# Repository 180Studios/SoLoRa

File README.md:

Board Features:

1. Low-cost components 

2. Easy (ish) Assembly. 
    a. Uses QFP package processor and 0603 Rs and Cs 
    b. Can be soldered by hand by most people using standard soldering iron 
    c. One exception is the accelerometer, which can be soldered using a reflow heat gun and a little training

3. Arduino compatible 
    a. Uses the same device as the Arduino Zero - can use Arduino bootloader. 

4. FeatherWing compatible 
    a. Can use with Adafruit’s featherwing expansion boards or use the header for a protoboard mezzanine 

5. Multiple power options to targeting wider IoT applications, particular field applications 
    a. Solar 
        i. Has a CR123 battery clip for a LiFePo4 battery used as a power reservoir. (400mAh) 
        ii. On-board regulator charges LiFePo4 to constant voltage. Solar cell size constrains max charge current. 
    b. Rechargeable Li-Po or external battery pack 
        i. For standard indoor applications 
        ii. On-board USB micro connector and charger IC 
    c. Lithium (primary cell) 
        i. Battery clip will also house a standard CR123 3V Lithium, which has ~1000mAH capacity 
    d. USB 5V for desktop development (or use with a USB battery bank?) 
    e. On- board adjustable regulator 
        i. Change Resistor values to adjust VDD 
            1. To drop Li-Po, external battery pack output voltage and USB 5V to safe level 
            2. LiFePo4 charge voltage. 
        ii. Regulator is used with Lithium primary battery 

6. Small size: 2.3 x 2 inches 
    a. Has mounting holes to match a inexpensive water tight enclosure 
    b. All components mount on one-size only. Bottom is free to increase mounting versatility. 
    c. 2-layer board, cheaper to fabricate. 

7. ARM Cortex M0 (SAMD20G18A) 

    a. Low power, high speed capable, 256K Flash 

8. Optional on-board sensors, indicators 
    a. 3-Axis Accelerometer 
    b. Temperature 
    c. Programmable Red LED 

9. Development Options 
    a. Arduino IDE (use as an Arduino Zero) 
    b. Atmel Studio 
        i. Atmel Studio has Arduino templates to program like Arduino, or: 
        ii. Use standard C form 
        iii. Full debugging capability (breakpoints, watch variables) 
            1. $20 JTAG debugger hardware required for this feature

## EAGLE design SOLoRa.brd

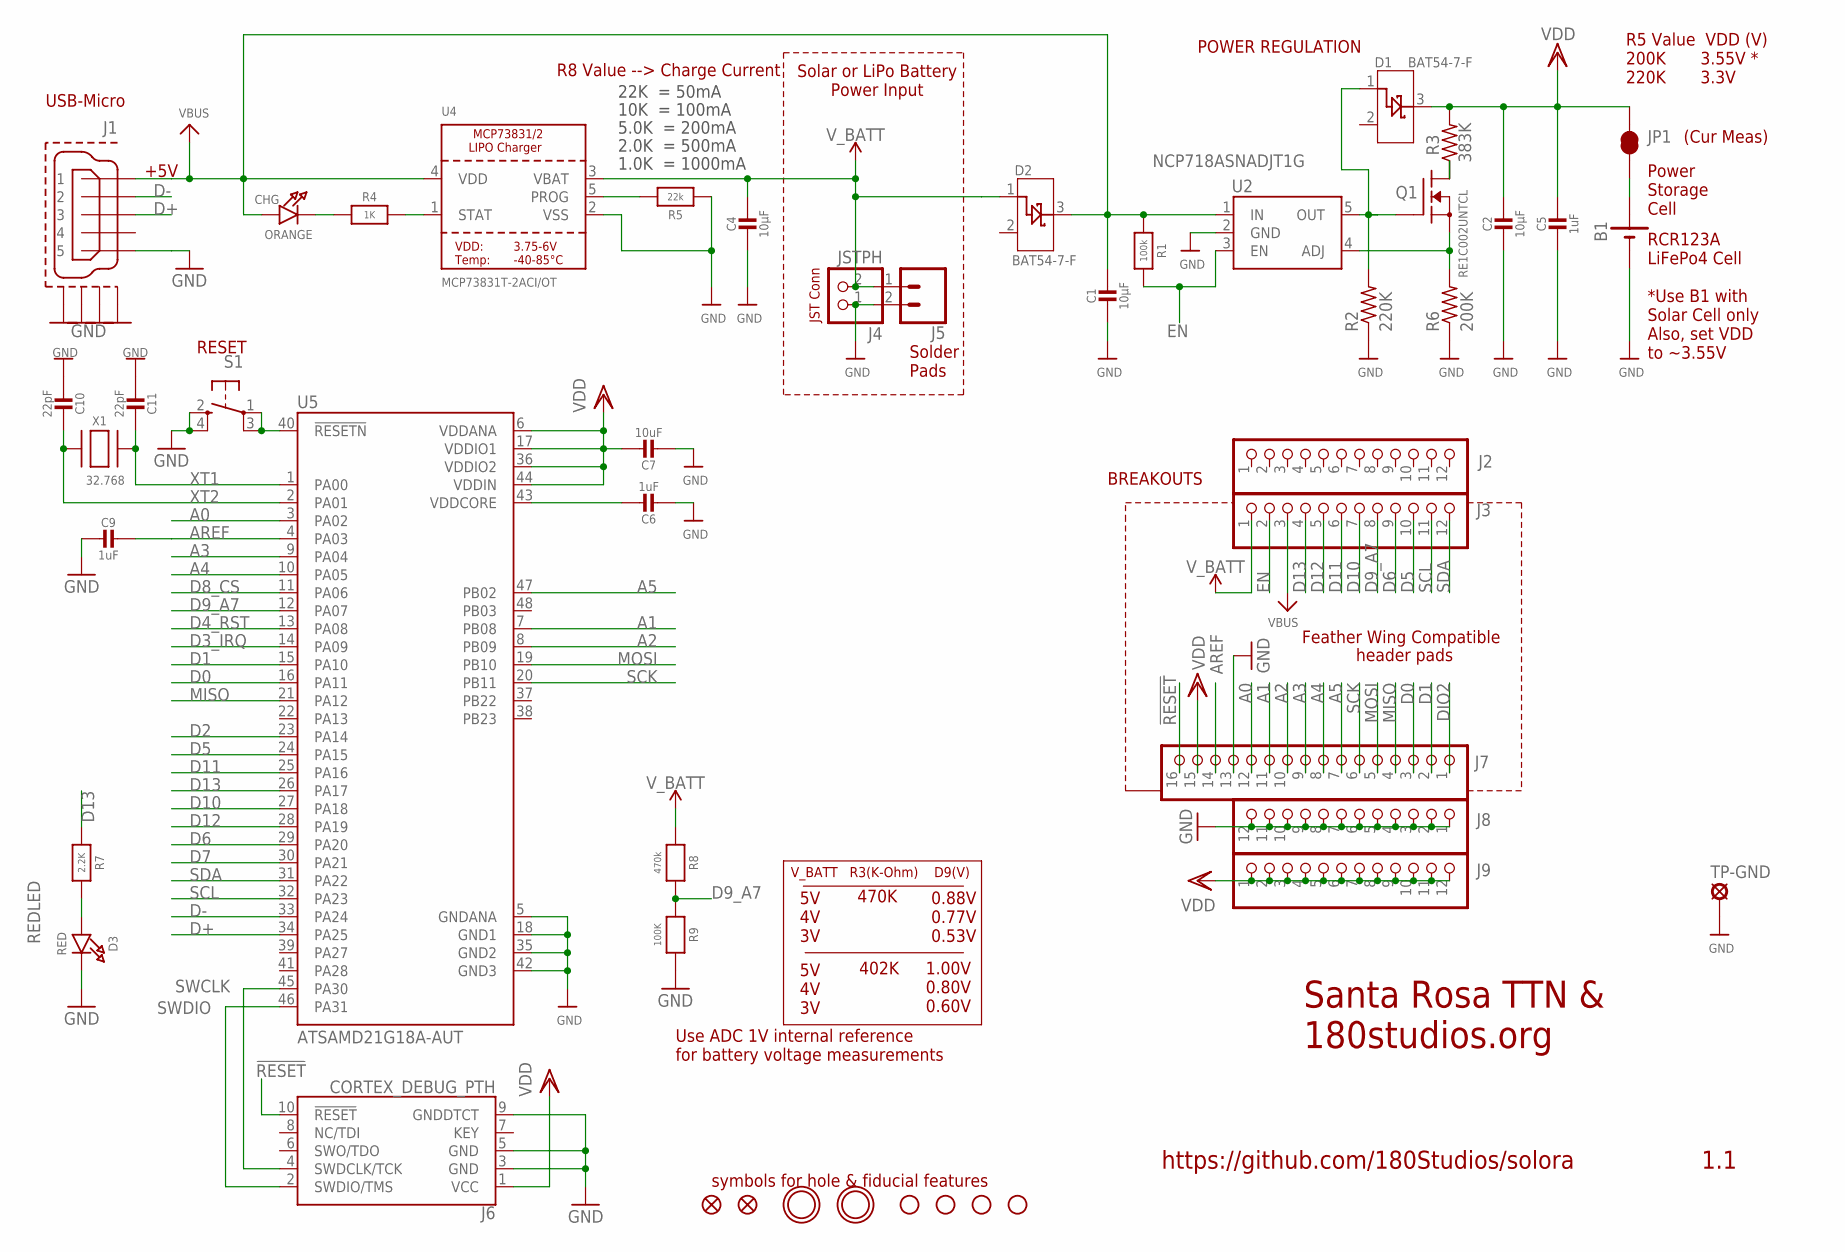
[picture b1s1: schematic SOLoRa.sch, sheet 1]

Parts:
$$U$1, $$U$4: FIDUCIAL""; FIDUCIAL_1MM
$$U$2, $$U$3: MOUNTINGHOLE2.5; MOUNTINGHOLE_2.5_PLATED
B1: BH123A
C1, C2, C4: 10µF; 0805-NO
C5, C6, C9: 1uF; 0603-NO
C7: 10uF; 0805-NO
C10, C11: 22pF; 0603-NO
CHG: ORANGE; CHIPLED_0805_NOOUTLINE
D1, D2: BAT54-7-F; SOT-23
D3: RED; CHIPLED_0805_NOOUTLINE
H1, H2, H3, H4: STAND-OFF
J1: CONN_USB-MIRCO_10118194; 10118194_USB
J2, J3, J8, J9: HEADER-1X12; 1X12_ROUND
J4: JSTPH; JSTPH2
J5: CONN_021X02_NO_SILK; 1X02_NO_SILK
J6: CORTEX_DEBUG_PTH; 2X5-PTH-1.27MM
J7: HEADER-1X16ROUND; 1X16_ROUND
JP1: JUMPER-SMT_2_NC_TRACE_NO-SILK; SMT-JUMPER_2_NC_TRACE_NO-SILK
Q1: RE1C002UNTCL; SOT50P160X85-3N
R1: 100k; 0603-NO
R2: 220K; R0603
R3: 383K; R0603
R4: 1K; 0603-NO
R5: 22k; 0603-NO
R6: 200K; R0603
R7: 2.2K; 0603-NO
R8: 470k; 0603-NO
R9: 100K; 0603-NO
S1: SPST_TACT-KMR2; KMR2
TP-GND: SE14
U2: NCP718ASNADJT1G; SOT95P280X100-5N
U4: MCP73831T-2ACI/OT; SOT23-5
U5: ATSAMD21G18A-AUT; QFP50P900X900X120-48N
X1: 32.768; XTAL3215

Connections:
!RESET: J6.10 (!RESET), J7.16, S1.1, S1.3 (P1), U5.40 (!RESETN)
A0: J7.12, U5.3 (PA02)
A1: J7.11, U5.7 (PB08)
A2: J7.10, U5.8 (PB09)
A3: J7.9, U5.9 (PA04)
A4: J7.8, U5.10 (PA05)
A5: J7.7, U5.47 (PB02)
ADJ1: Q1.3 (D), R3.1
AREF: C9.1, J7.14, U5.4 (PA03)
CHGLED: CHG.C, R4.1
D0: J7.3, U5.16 (PA11)
D1: J7.2, U5.15 (PA10)
D2: U5.23 (PA14)
D3_IRQ: U5.14 (PA09); also elsewhere on the board
D4_RST: U5.13 (PA08); also elsewhere on the board
D5: J3.10, U5.24 (PA15)
D6: J3.9, U5.29 (PA20); also elsewhere on the board
D7: U5.30 (PA21)
D8_CS: U5.11 (PA06); also elsewhere on the board
D9_A7: J3.8, R8.2, R9.1, U5.12 (PA07)
D10: J3.7, U5.27 (PA18)
D11: J3.6, U5.25 (PA16); also elsewhere on the board
D12: J3.5, U5.28 (PA19)
D13: J3.4, R7.1, U5.26 (PA17)
D+: J1.3, U5.34 (PA25)
D-: J1.2, U5.33 (PA24)
DIO2: J7.1; also elsewhere on the board
EN: J3.2, R1.2, U2.3 (EN)
GND: B1.MINUS, C1.2, C2.2, C4.2, C5.2, C6.2, C7.2, C9.2, C10.2, C11.2, D3.C, J1.5, J1.6 (GND1), J1.7 (GND2), J1.8 (GND3), J1.9 (GND4), J4.1, J5.2, J6.3 (GND), J6.5 (GND), J6.9 (GNDDTCT), J7.13, J8.1, J8.2, J8.3, J8.4, J8.5, J8.6, J8.7, J8.8, J8.9, J8.10, J8.11, J8.12, R2.1, R5.2, R6.1, R9.2, S1.2 (S), S1.4 (S1), TP-GND.MP, U2.2 (GND), U4.2 (VSS), U5.5 (GNDANA), U5.18 (GND1), U5.35 (GND2), U5.42 (GND3); also elsewhere on the board
MISO: J7.4, U5.21 (PA12); also elsewhere on the board
MOSI: J7.5, U5.19 (PB10); also elsewhere on the board
PLUS: B1.PLUS, JP1.1
PROG: R5.1, U4.5 (PROG)
REDLED: D3.A, R7.2
REGADJ: Q1.2 (S), R6.2, U2.4 (ADJ)
REGOUT: D1.1 (EPAD1), Q1.1 (G), R2.2, U2.5 (OUT)
SCK: J7.6, U5.20 (PB11); also elsewhere on the board
SCL: J3.11, U5.32 (PA23); also elsewhere on the board
SDA: J3.12, U5.31 (PA22); also elsewhere on the board
STAT: R4.2, U4.1 (STAT)
SWCLK: J6.4 (SWDCLK/TCK), U5.45 (PA30)
SWDIO: J6.2 (SWDIO/TMS), U5.46 (PA31)
VBUS: C1.1, CHG.A, D2.3 (EPAD3), J1.1, J3.3, R1.1, U2.1 (IN), U4.4 (VDD)
VDD: C2.1, C5.1, C7.1, D1.3 (EPAD3), J6.1 (VCC), J7.15, J9.1, J9.2, J9.3, J9.4, J9.5, J9.6, J9.7, J9.8, J9.9, J9.10, J9.11, J9.12, JP1.2, R3.2, U5.6 (VDDANA), U5.17 (VDDIO1), U5.36 (VDDIO2), U5.44 (VDDIN); also elsewhere on the board
VDDCORE: C6.1, U5.43 (VDDCORE)
V_BATT: C4.1, D2.1 (EPAD1), J3.1, J4.2, J5.1, R8.1, U4.3 (VBAT)
XT1: C11.1, U5.1 (PA00), X1.P$1
XT2: C10.1, U5.2 (PA01), X1.P$2

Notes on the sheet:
POWER REGULATION
RESET
10K = 100mA
5.0K = 200mA
2.0K = 500mA
1.0K = 1000mA
BREAKOUTS
R5 Value VDD (V) 200K 3.55V * 220K 3.3V
22K = 50mA
RCR123A LiFePo4 Cell *Use B1 with Solar Cell only Also, set VDD to ~3.55V
Solar or LiPo Battery Power Input
Power Storage Cell
JST Conn
Solder Pads
R8 Value --> Charge Current
1.1
Santa Rosa TTN & 180studios.org
https://github.com/180Studios/solora
USB-Micro
+5V
Feather Wing Compatible
header pads
V_BATT R3(K-Ohm) D9(V)
5V 4V 3V
470K
402K
0.88V 0.77V 0.53V
1.00V 0.80V 0.60V
Use ADC 1V internal reference for battery voltage measurements
symbols for hole & fiducial features
(Cur Meas)

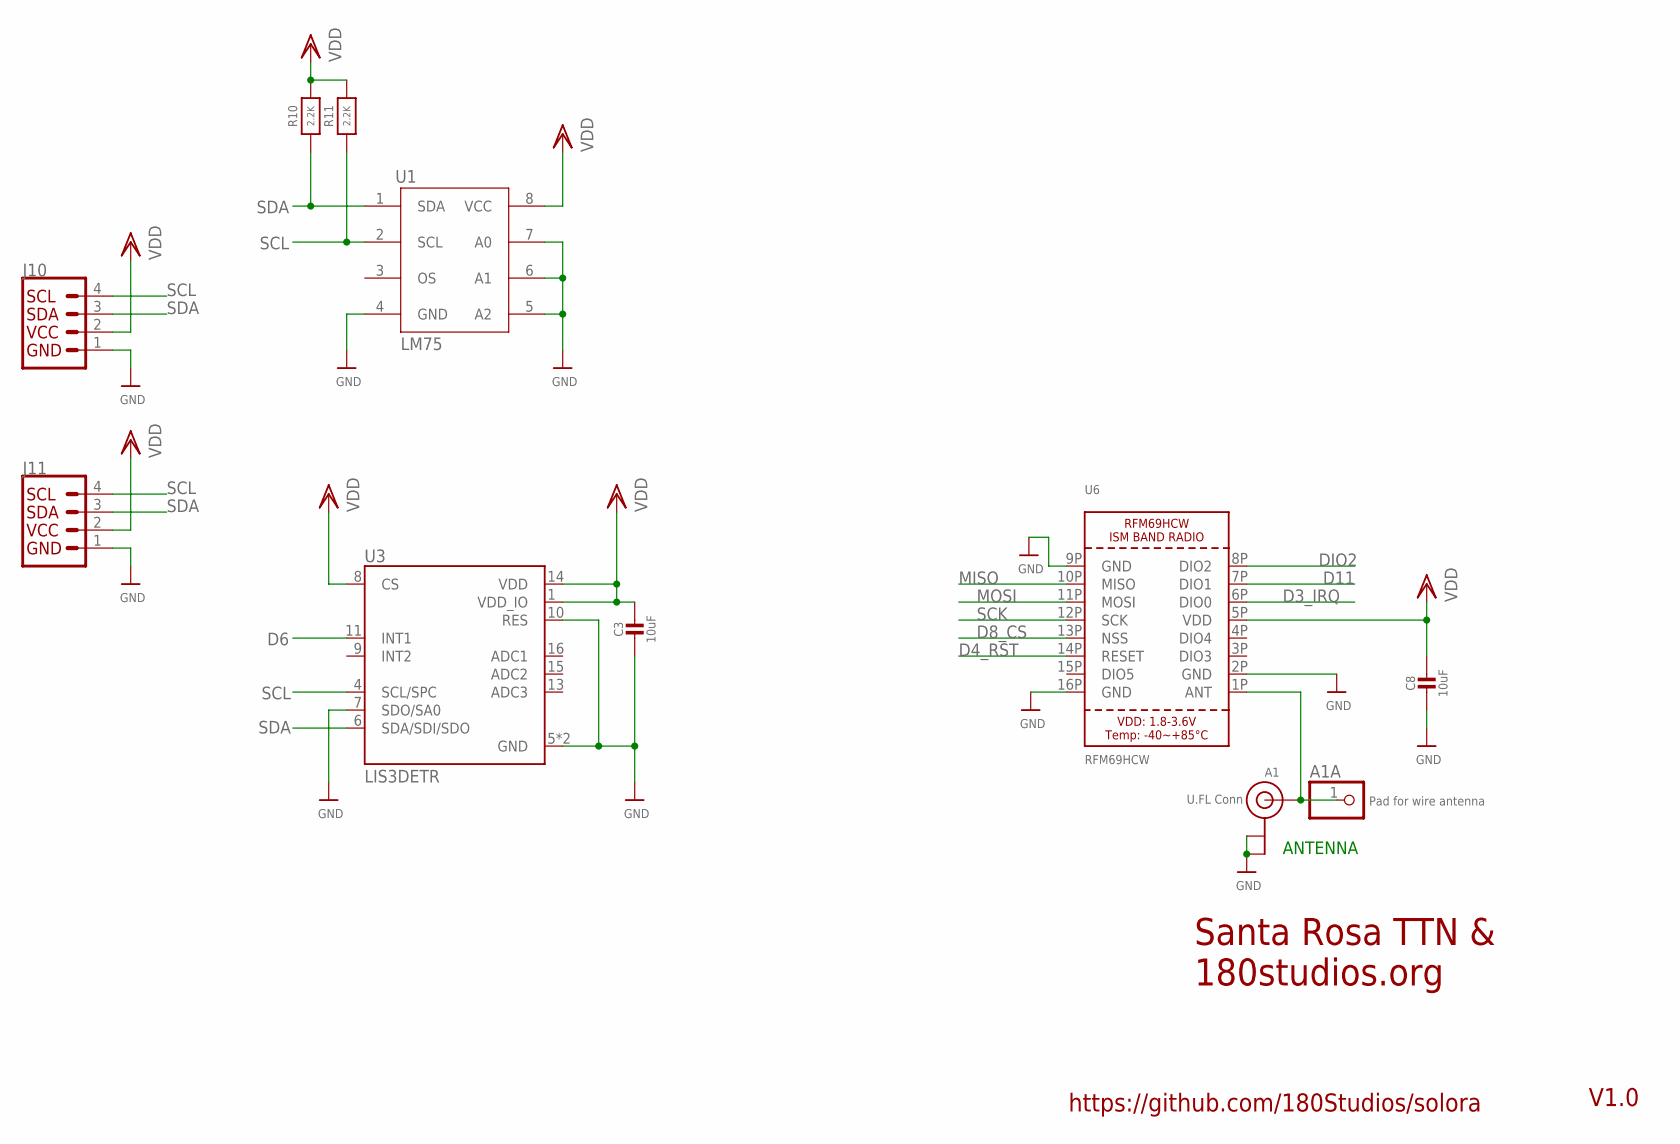
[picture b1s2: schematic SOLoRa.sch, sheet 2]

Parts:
A1: U.FL Conn; U.FL
A1A: Pad for wire antenna; 1X01_ROUND
C3, C8: 10uF; 0805-NO
J10, J11: QWIIC_CONNECTORJS-1MM; 1X04_1MM_RA
R10, R11: 2.2K; 0603-NO
U1: LM75; SO8
U3: LIS3DETR; LGA16R50P5X3_300X300X100N
U6: RFM69HCW; RFMHCW_SMT

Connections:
ANT: A1.3 (SIGNAL), A1A.1, U6.1P (ANT)
D3_IRQ: U6.6P (DIO0); also elsewhere on the board
D4_RST: U6.14P (RESET); also elsewhere on the board
D6: U3.11 (INT1); also elsewhere on the board
D8_CS: U6.13P (NSS); also elsewhere on the board
D11: U6.7P (DIO1); also elsewhere on the board
DIO2: U6.8P (DIO2); also elsewhere on the board
GND: A1.1 (GND), A1.2 (GND), C3.2, C8.2, J10.1, J11.1, U1.4 (GND), U1.5 (A2), U1.6 (A1), U1.7 (A0), U3.5 (GND), U3.7 (SDO/SA0), U3.10 (RES), U3.12 (GND), U6.2P (GND), U6.9P (GND), U6.16P (GND); also elsewhere on the board
MISO: U6.10P (MISO); also elsewhere on the board
MOSI: U6.11P (MOSI); also elsewhere on the board
SCK: U6.12P (SCK); also elsewhere on the board
SCL: J10.4, J11.4, R11.1, U1.2 (SCL), U3.4 (SCL/SPC); also elsewhere on the board
SDA: J10.3, J11.3, R10.1, U1.1 (SDA), U3.6 (SDA/SDI/SDO); also elsewhere on the board
VDD: C3.1, C8.1, J10.2, J11.2, R10.2, R11.2, U1.8 (VCC), U3.1 (VDD_IO), U3.8 (CS), U3.14 (VDD), U6.5P (VDD); also elsewhere on the board

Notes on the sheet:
ANTENNA
Santa Rosa TTN & 180studios.org
V1.0
https://github.com/180Studios/solora

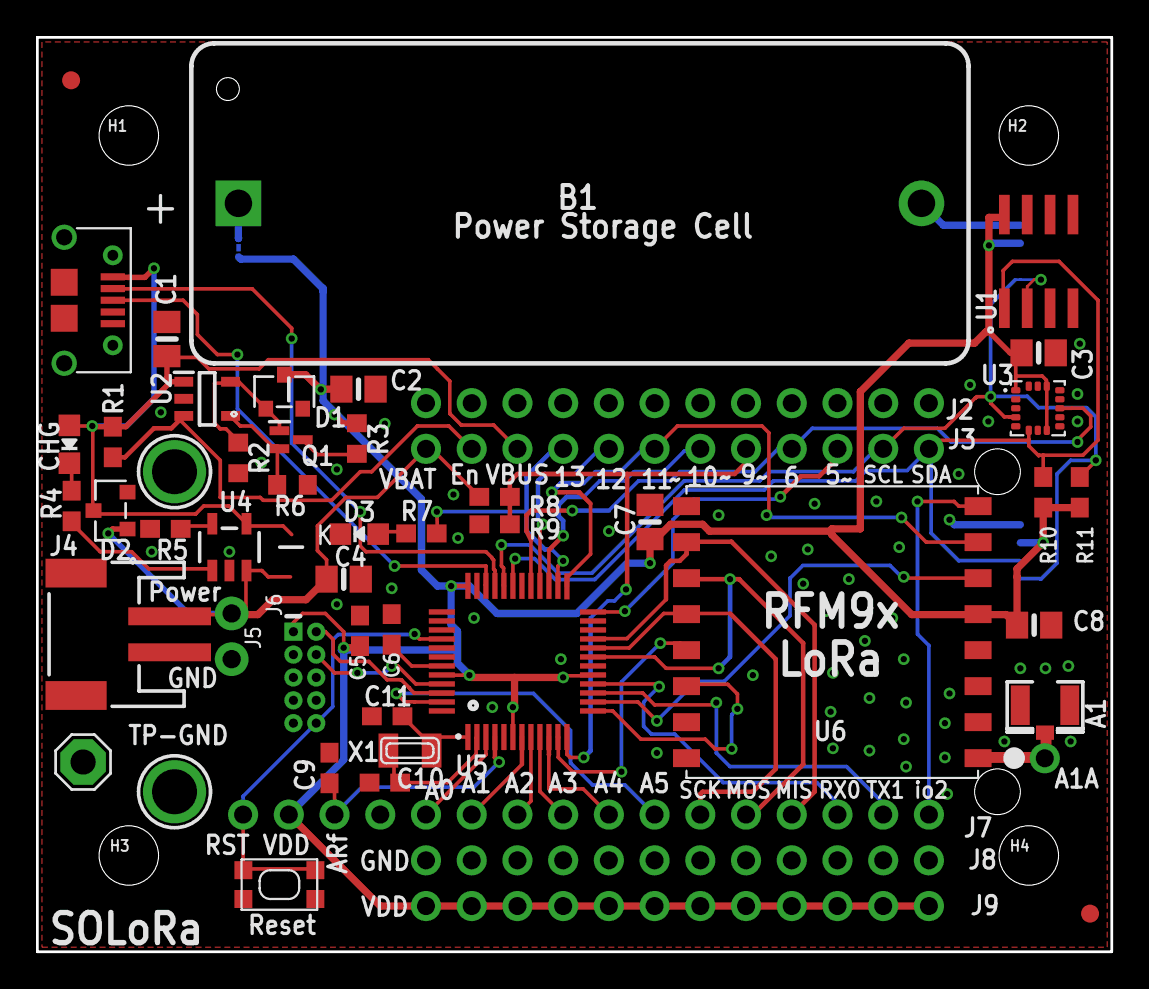
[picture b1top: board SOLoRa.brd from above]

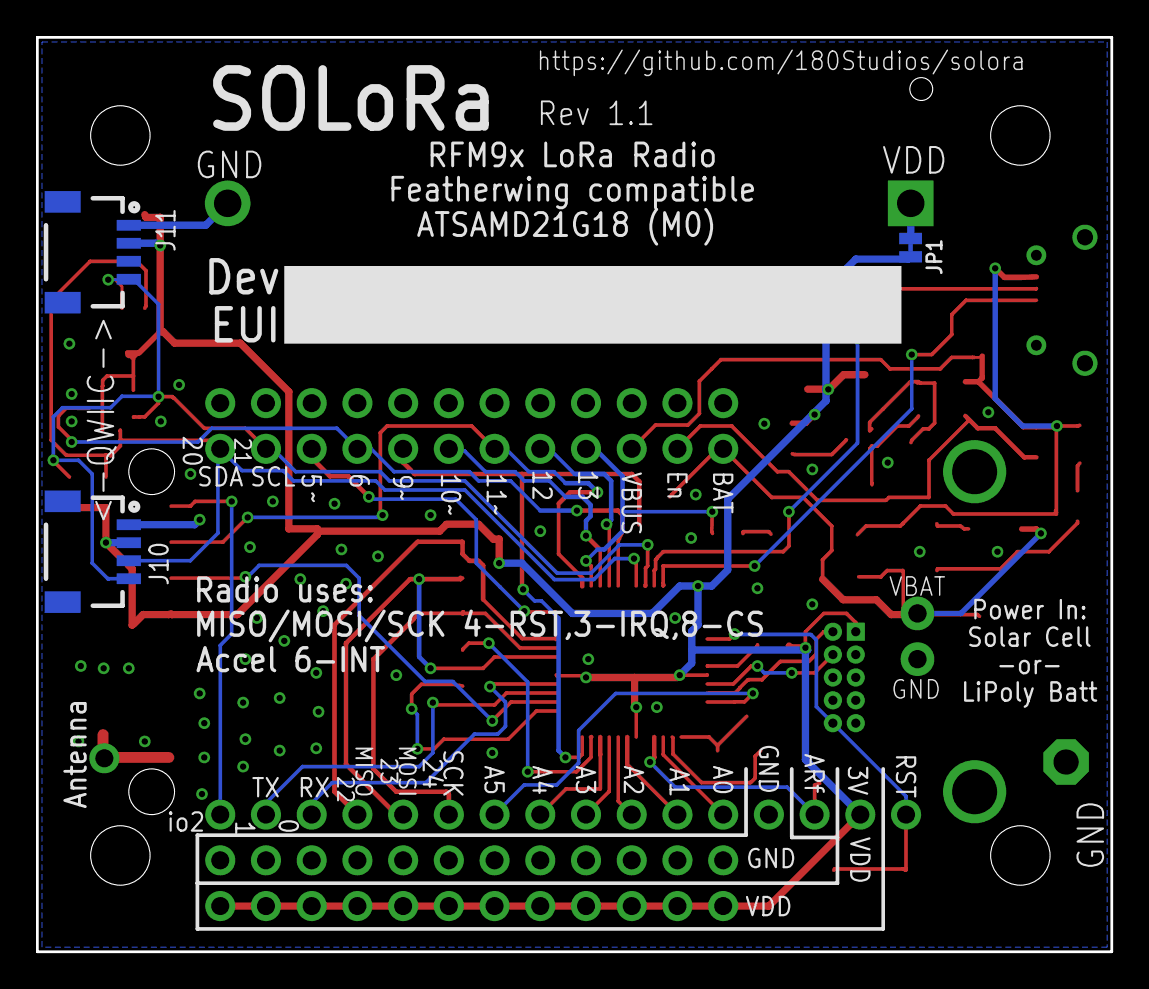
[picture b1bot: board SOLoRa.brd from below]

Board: 2 copper layers, 59.7 x 50.8 mm, 59 parts (3 on the bottom side), 47 nets.

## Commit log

2018-07-04 Added first draft BOM
2018-07-05 cosmetic changes to schematic
2018-08-15 Version 1.1

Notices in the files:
parts and their libraries:
microbuilder: This work is placed in the public domain, and may be freely used for commercial and non-commercial work with the following conditions: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
SparkFun-Hardware: Licensing: Creative Commons ShareAlike 4.0 International - https://creativecommons.org/licenses/by-sa/4.0
